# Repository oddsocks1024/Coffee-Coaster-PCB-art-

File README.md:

# Coffee Coaster PCB (art)

## Description
Novelty coffee coasters made out of PCB with electronic related puns. Includes a 3D printable holder for up to 5 coasters.

## Support Me
* [My Projects](https://projects.amiga-hardware.com) - Donate on this page
* [Order the Coffee Coaster PCB](https://www.pcbway.com/project/shareproject/PCB_Coffee_Coasters_0daa50d3.html)
* [Order the Coffee Coaster Holder](https://www.pcbway.com/project/shareproject/Holder_for_PCB_Coffee_Coasters_4daf9a84.html)

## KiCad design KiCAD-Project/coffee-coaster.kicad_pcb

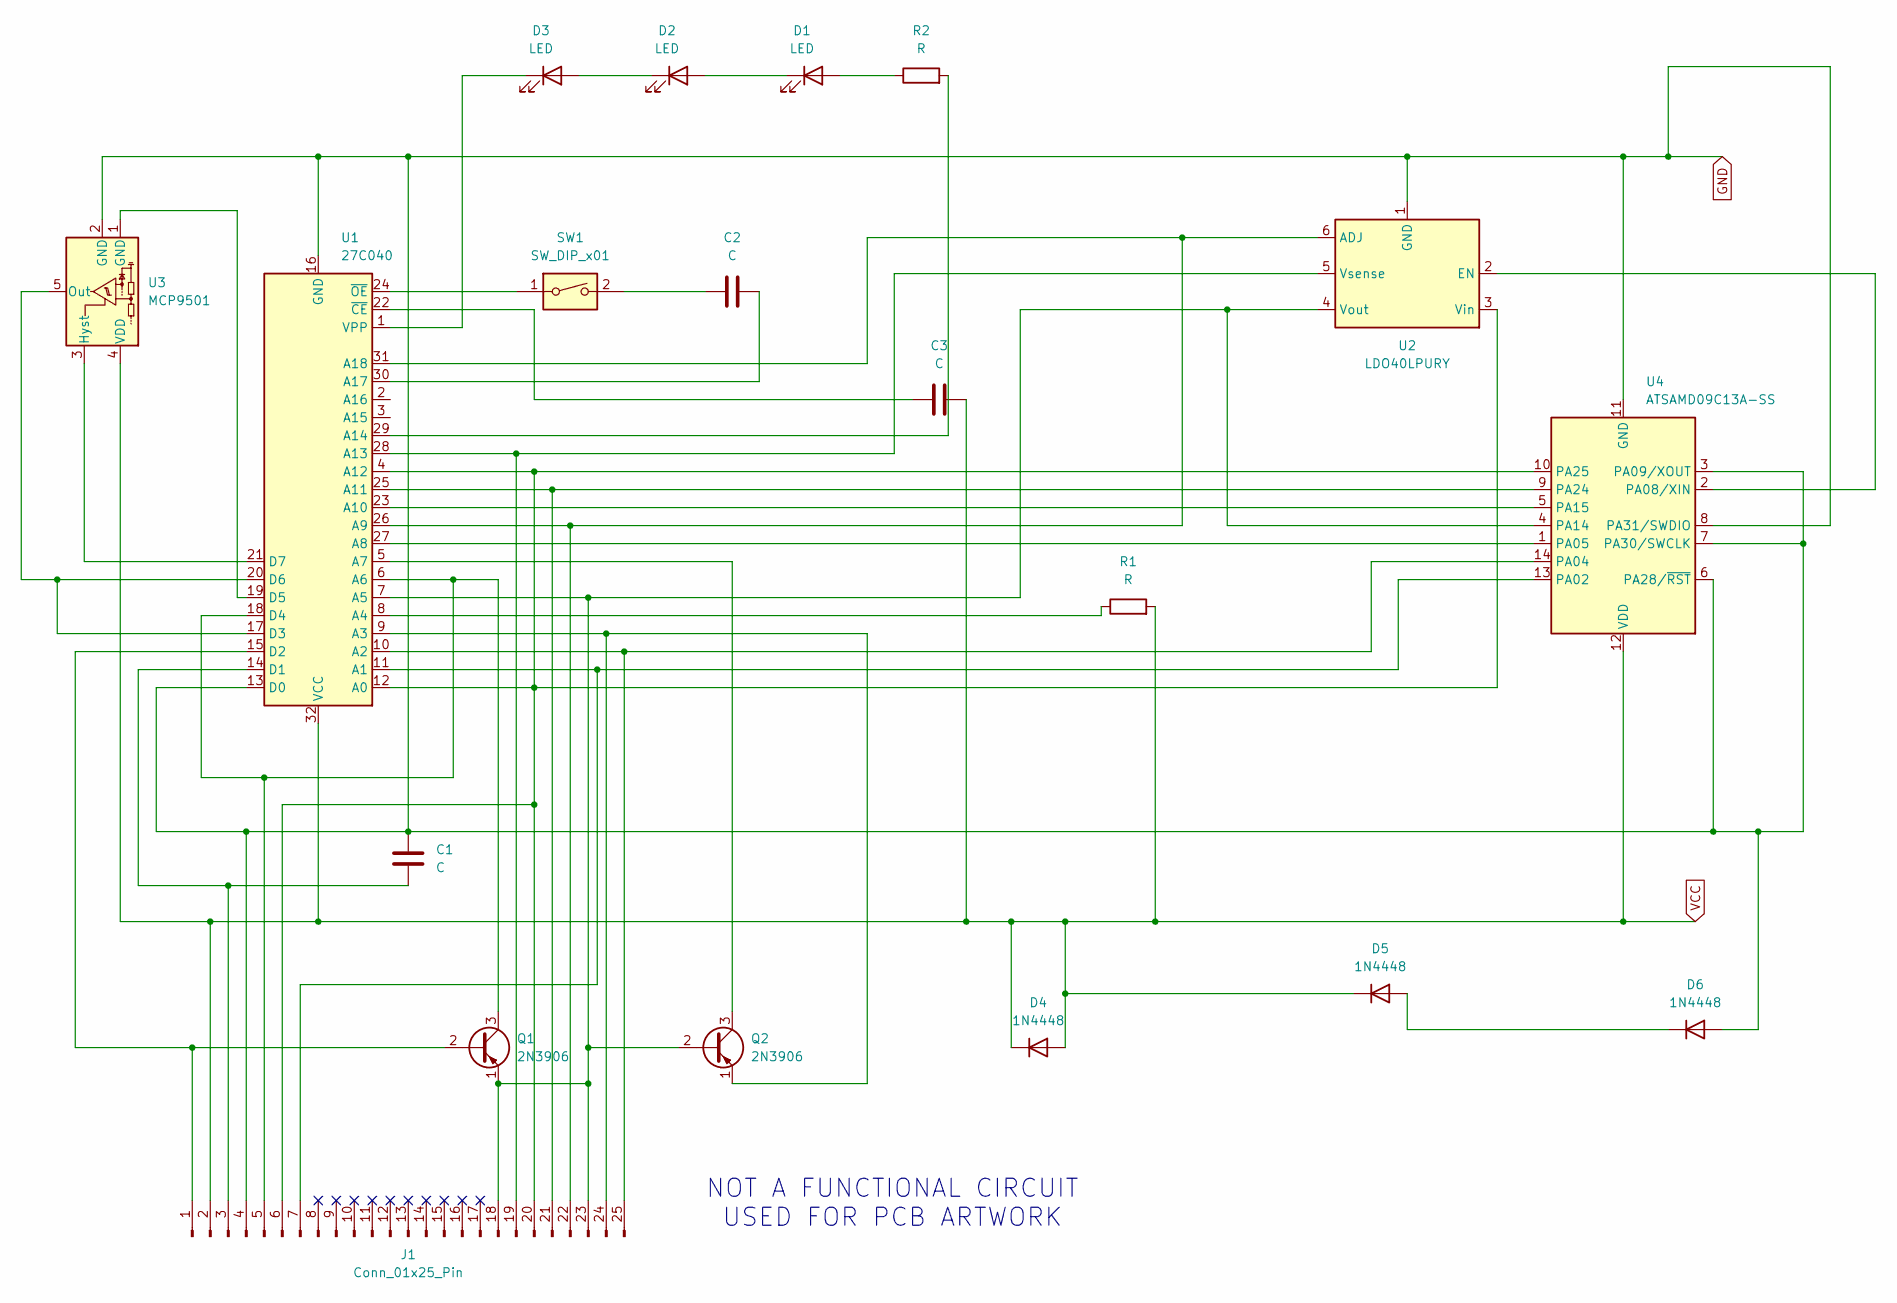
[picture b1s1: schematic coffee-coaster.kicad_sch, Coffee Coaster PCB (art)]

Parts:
C1, C2, C3: C; C_Axial_L5.1mm_D3.1mm_P7.50mm_Horizontal
D1, D2, D3: LED; LED_D5.0mm
D4, D5, D6: 1N4448; D_DO-35_SOD27_P7.62mm_Horizontal
J1: Conn_01x25_Pin; DSUB-25_Socket_Horizontal_P2.77x2.84mm_EdgePinOffset9.40mm
Q1, Q2: 2N3906; TO-92_Inline
R1, R2: R; R_Axial_DIN0207_L6.3mm_D2.5mm_P7.62mm_Horizontal
SW1: SW_DIP_x01; SW_DIP_SPSTx01_Piano_10.8x4.1mm_W7.62mm_P2.54mm
U1: 27C040; DIP-32_W15.24mm_Socket
U2: LDO40LPURY; DFN-6-1EP_3x3mm_P0.95mm_EP1.7x2.6mm
U3: MCP9501; SOT-23-5
U4: ATSAMD09C13A-SS; SOIC-14_3.9x8.7mm_P1.27mm

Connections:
GND: C1.1, D6.2 (A), J1.4, U1.13 (D0), U1.16 (GND), U2.1 (GND), U2.7 (GND), U3.2 (GND), U4.3 (PA09/XOUT), U4.6 (PA28/~RST), U4.7 (PA30/SWCLK), U4.8 (PA31/SWDIO), U4.11 (GND)
unnamed: C2.2, SW1.2
unnamed: D1.2 (A), R2.1
unnamed: D1.1 (K), D2.2 (A)
unnamed: D2.1 (K), D3.2 (A)
unnamed: D3.1 (K), U1.1 (VPP)
unnamed: D5.2 (A), D6.1 (K)
unnamed: J1.1, Q1.2 (B), U1.15 (D2)
unnamed: C1.2, J1.3, U1.14 (D1)
unnamed: J1.5, Q1.3 (C), U1.6 (A6), U1.18 (D4)
unnamed: J1.7, U1.11 (A1), U4.13 (PA02)
unnamed: J1.18, J1.23, Q1.1 (E), Q2.2 (B), U1.7 (A5), U2.4 (Vout), U4.4 (PA14)
unnamed: J1.19, U1.28 (A13), U2.5 (Vsense)
unnamed: J1.6, J1.20, U1.4 (A12), U1.12 (A0), U2.3 (Vin), U4.10 (PA25)
unnamed: J1.21, U1.25 (A11), U4.9 (PA24)
unnamed: J1.22, U1.26 (A9), U1.31 (A18), U2.6 (ADJ)
unnamed: J1.24, Q2.1 (E), U1.9 (A3)
unnamed: J1.25, U1.10 (A2), U4.14 (PA04)
unnamed: Q2.3 (C), U1.5 (A7)
unnamed: R1.1, U1.8 (A4)
unnamed: U1.27 (A8), U4.1 (PA05)
unnamed: U1.23 (A10), U4.5 (PA15)
unnamed: R2.2, U1.29 (A14)
unnamed: C2.1, U1.30 (A17)
unnamed: U1.17 (D3), U1.20 (D6), U3.5 (Out)
unnamed: U1.19 (D5), U3.1 (GND)
unnamed: U1.21 (D7), U3.3 (Hyst)
unnamed: C3.1, U1.22 (~CE)
unnamed: SW1.1, U1.24 (~OE)
unnamed: U2.2 (EN), U4.2 (PA08/XIN)
VCC: C3.2, D4.1 (K), D4.2 (A), D5.1 (K), J1.2, R1.2, U1.32 (VCC), U3.4 (VDD), U4.12 (VDD)

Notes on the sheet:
NOT A FUNCTIONAL CIRCUIT USED FOR PCB ARTWORK

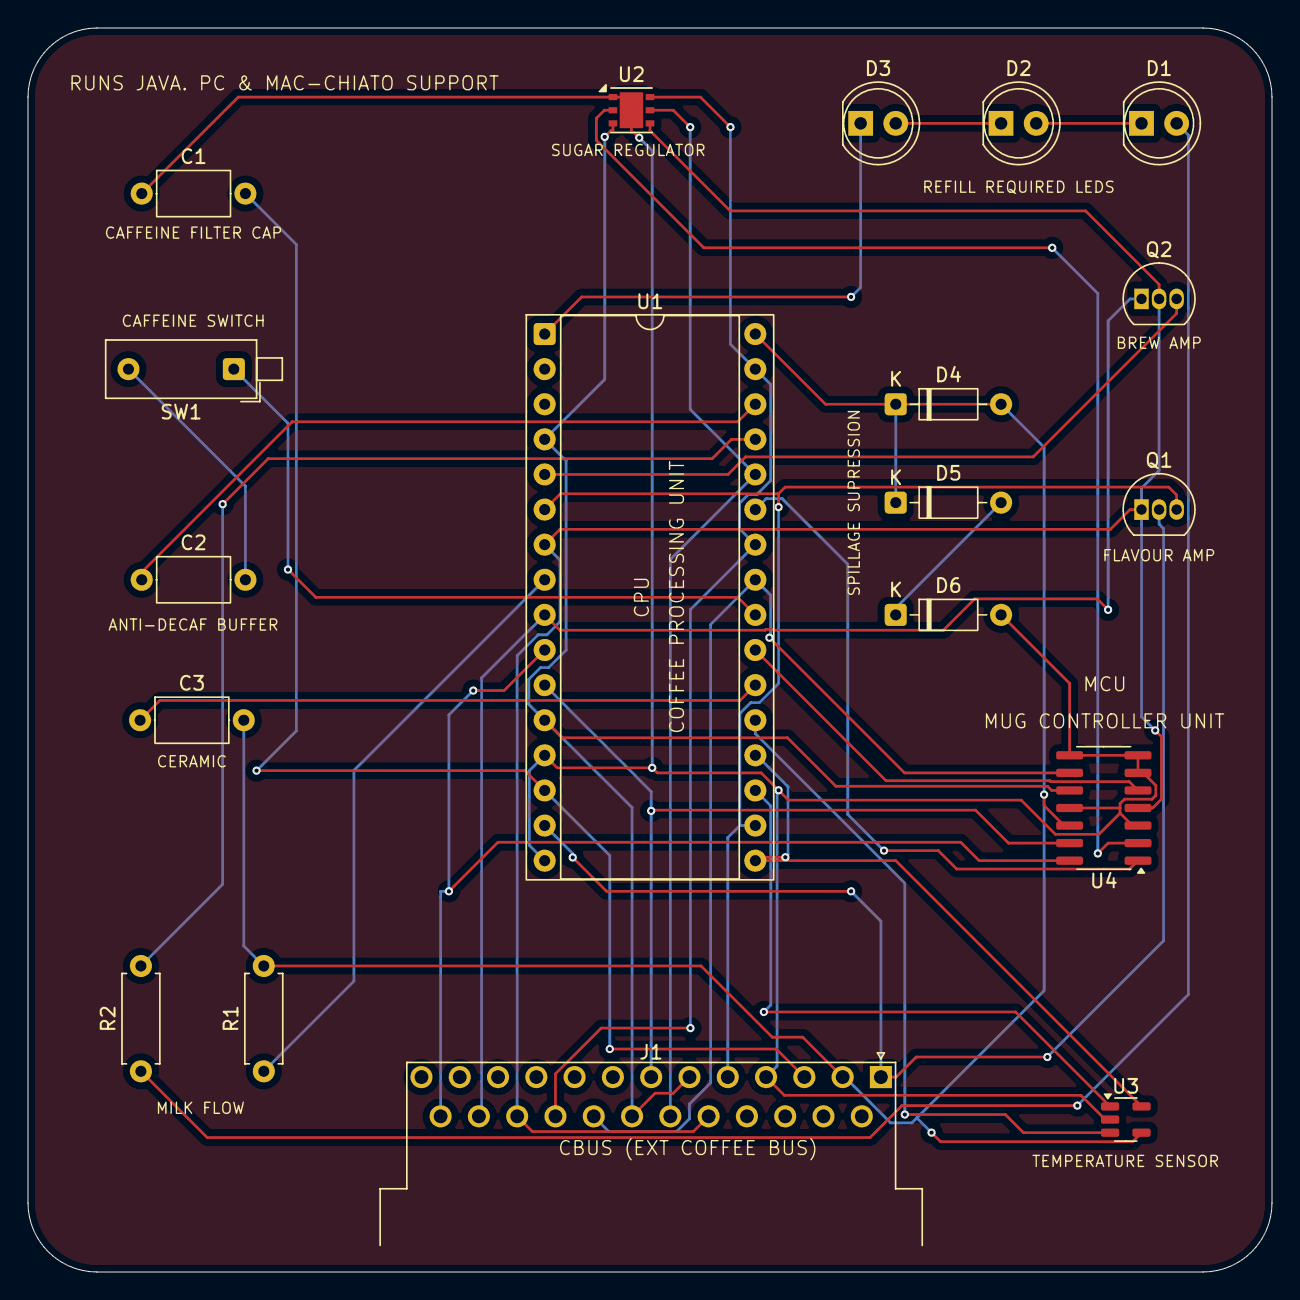
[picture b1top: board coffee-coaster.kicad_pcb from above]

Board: 2 copper layers, 90.0 x 90.0 mm, 19 parts (0 on the bottom side), 31 nets.

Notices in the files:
KiCAD-Project/coffee-coaster.kicad_pcb:
©2025 b5s4
